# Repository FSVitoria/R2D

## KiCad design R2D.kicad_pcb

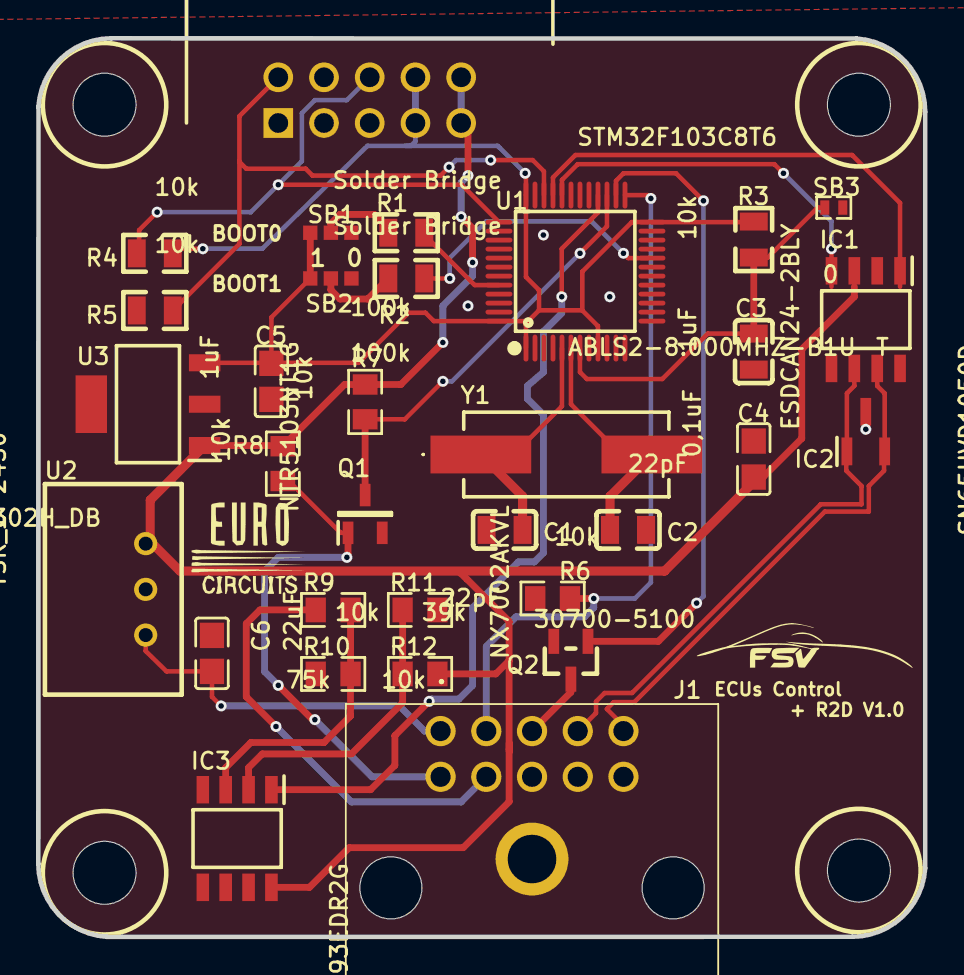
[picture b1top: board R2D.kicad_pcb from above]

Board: 2 copper layers, 49.3 x 49.9 mm, 36 parts (0 on the bottom side), 26 nets.

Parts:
C1, C2: 22pF; C0805
C3, C5: 1uF; C0805
C4: 0,1uF; C0805
C6: 22uF; C0805
Hole_gge6901: Hole_gge6901
Hole_gge7163: Hole_gge7163
Hole_gge7279: Hole_gge7279
Hole_gge10533: Hole_gge10533
IC1: SN65HVD1050D; SOIC127P600X175-8N
IC2: ESDCAN24-2BLY; SOT105P255X150-3N
IC3: LM393EDR2G; SOIC127P600X175-8N
J1: 30700-5100; 307005100
J2: 61201021721; SHDRRA10W64P254X254_2X5_2036X8
Q1: NTR5103NT1G; SOT95P237X101-3N
Q2: NX7002AKVL; TO-236AB_L2.9-W1.3-P0.95-LS2.3-BR
R1, R2: 100k; R0805
R3, R4, R5: 10k; R0805
R6, R7, R8, R10, R11: 10k; R0805_NEW
R9: 75k; R0805_NEW
R12: 39k; R0805_NEW
SB1, SB2: Solder Bridge; SOLDER BRDIGE
SB3: 0; R0402
U1: STM32F103C8T6; LQFP-48_L7.0-W7.0-P0.50-LS9.0-BL
U2: TSR_1-2450; TSR-1-24120
U3: MCP1799T-3302H_DB; SOT230P700X180-4N
Y1: ABLS2-8.000MHZ-B1U-T; ABLS

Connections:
3V3: C5.2, J2.7, J2.8, R3.2, R4.2, SB1.1, SB2.1, U1.1, U1.9, U1.24, U1.36, U1.48, U3.3
+5V: C4.1, IC1.3, IC3.8, J2.9, J2.10, R7.2, R8.2, R12.2, U2.3, U3.1
+24V: C6.2, J1.1, U2.1
BOOT0: R1.1, U1.44
BOOT1: R2.1, U1.20
BUZZER: Q2.1, U1.26
C1_1: C1.1, U1.5, Y1.1
C2_1: C2.1, U1.6, Y1.2
CAN_H: IC1.7, IC2.2, J1.5
CAN_L: IC1.6, IC2.1, J1.4
CAN_RX: IC1.4, U1.32
CAN_TX: IC1.1, U1.33
GND: C1.2, C2.2, C3.1, C4.2, C5.1, C6.1, IC1.2, IC1.8, IC2.3, IC3.4, IC3.5, IC3.6, IC3.7, J1.8, J1.9, J2.3, J2.4, Q1.2, Q2.2, R5.1, R6.1, R10.1, R11.1, SB1.3, SB2.3, SB3.1, U1.8, U1.23, U1.35, U1.47, U2.2, U3.2, U3.4
IC3_2: IC3.2, R11.2, R12.1
IC3_3: IC3.3, R9.1, R10.2
Q2_3: J1.3, Q2.3
R1_2: R1.2, SB1.2
R2D_BUTTON: J1.2, R6.2, U1.25
R2_2: R2.2, SB2.2
RST: C3.2, R3.1, SB3.2, U1.7
SDC+: J1.7, R9.2
SDC_DETECTION: IC3.1, U1.28
SWCLK: J2.6, R4.1, U1.37
SWDIO: J2.2, R5.2, U1.34
TS_STATE: J1.6, Q1.1, R8.1
TS_STATE_DETECTION: Q1.3, R7.1, U1.27
